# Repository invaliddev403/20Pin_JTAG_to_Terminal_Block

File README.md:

# 20Pin_JTAG_to_Terminal_Block
A 20 Pin JTAG to Terminal Block Adapter

Designed to make it easier to add a JTAG debugger to a board with flying leads.

* Terminal Block: 1742059 from Phoenix Contact
* 20 Pin Header Connector (with alignment shroud): HIF3FC-20PA-2.54DSA(71) from Hirose Connector
* 2 Pin Jumpers I used available 2.54 pitch through-hole connectors I had lying around.

Design files made with KiCAD 7.0

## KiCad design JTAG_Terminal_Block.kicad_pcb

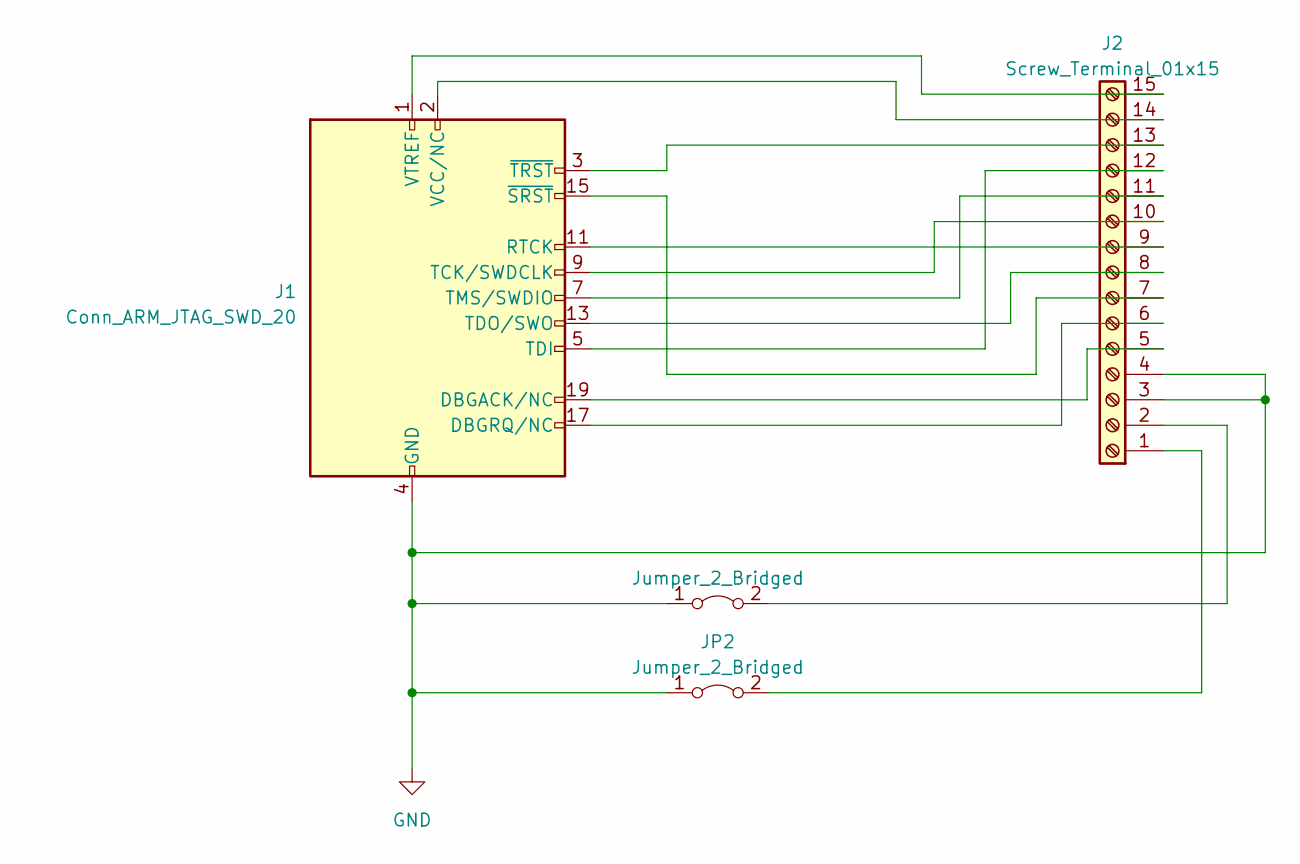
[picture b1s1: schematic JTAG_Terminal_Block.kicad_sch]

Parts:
J1: Conn_ARM_JTAG_SWD_20; IDC-Header_2x10_P2.54mm_Horizontal
J2: Screw_Terminal_01x15; TerminalBlock_Phoenix_MKDS-1,5-15_1x15_P5.00mm_Horizontal
JP1, JP2: Jumper_2_Bridged; PinHeader_1x02_P2.54mm_Vertical

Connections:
GND: J1.4 (GND), J1.6 (GND), J1.8 (GND), J1.10 (GND), J1.12 (GND), J1.14 (GND), J1.16 (GND), J1.18 (GND), J1.20 (GND), J2.3, J2.4, JP1.1 (A), JP2.1 (A)
unnamed: J1.19 (DBGACK/NC), J2.5
unnamed: J1.17 (DBGRQ/NC), J2.6
unnamed: J1.11 (RTCK), J2.9
unnamed: J1.9 (TCK/SWDCLK), J2.10
unnamed: J1.5 (TDI), J2.12
unnamed: J1.13 (TDO/SWO), J2.8
unnamed: J1.7 (TMS/SWDIO), J2.11
unnamed: J1.2 (VCC/NC), J2.14
unnamed: J1.1 (VTREF), J2.15
unnamed: J1.15 (~SRST), J2.7
unnamed: J1.3 (~TRST), J2.13
unnamed: J2.1, JP2.2 (B)
unnamed: J2.2, JP1.2 (B)

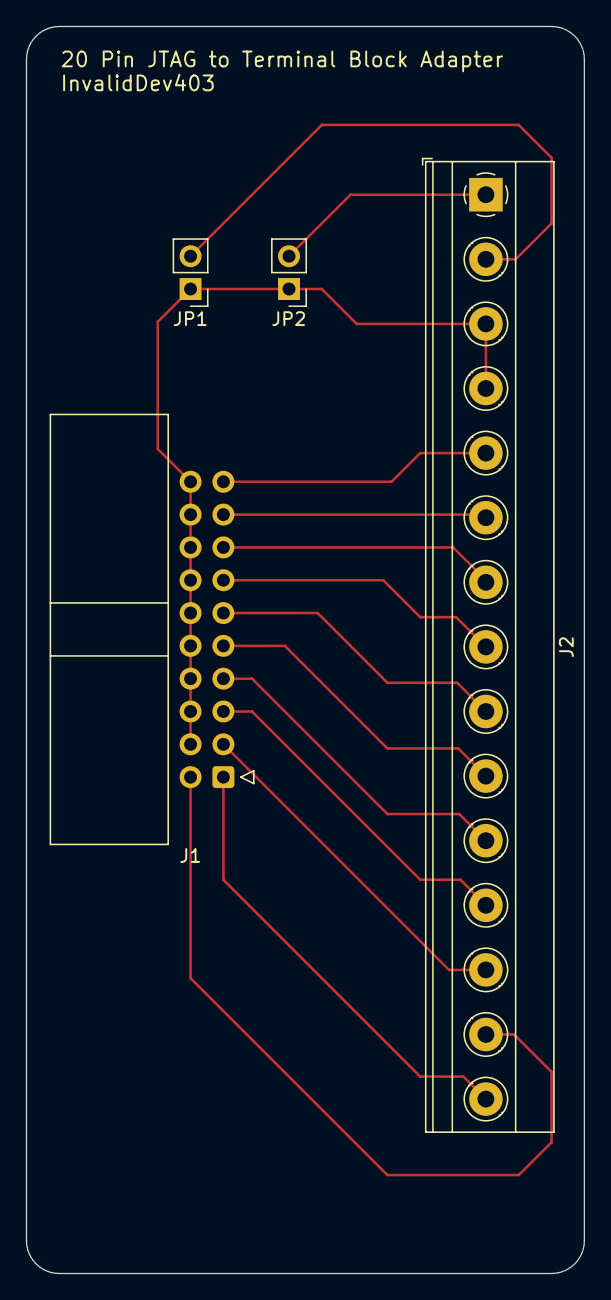
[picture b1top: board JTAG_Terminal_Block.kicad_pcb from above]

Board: 2 copper layers, 43.2 x 96.5 mm, 4 parts (0 on the bottom side), 14 nets.
